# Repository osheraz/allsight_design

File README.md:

# allsight_design

Manufacturing design files for the [AllSight tactile sensor](https://github.com/osheraz/allsight).

## Content

This repository aims to provide manufacturing, assembly, and quick-start instruction for the AllSight tactile sensor.

## Quick Start

Manufacturing and assembly documentation is found in the [Quick Start Guide](https://docs.google.com/document/d/1w17rNp5aecgzT3BPEN_t8wV7Ci-CQgCzxq583NlFb_A/edit?usp=sharing)

## Questions and Contributing

If you have questions or need help with the content of this repo please open a ticket.

## License
These design files are licensed under CC-by-NC, as found in the [LICENSE](LICENSE) file.

## Citing
If you use this project in your research, please cite this [paper](https://arxiv.org/abs/2307.02928):

```BibTeX
@misc{azulay2023allsight,
      title={AllSight: A Low-Cost and High-Resolution Round Tactile Sensor with Zero-Shot Learning Capability}, 
      author={Osher Azulay and Nimrod Curtis and Rotem Sokolovsky and Guy Levitski and Daniel Slomovik and Guy Lilling and Avishai Sintov},
      year={2023},
      eprint={2307.02928},
      archivePrefix={arXiv},
      primaryClass={cs.RO}
}

```

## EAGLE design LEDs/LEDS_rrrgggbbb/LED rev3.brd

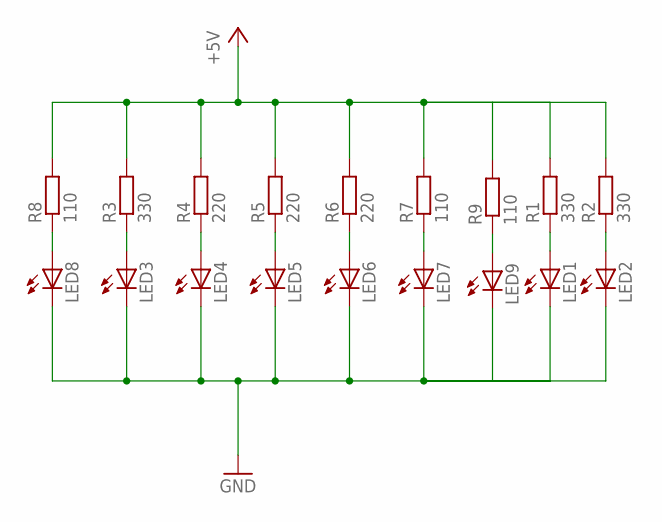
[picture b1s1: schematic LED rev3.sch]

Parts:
LED1, LED2, LED3, LED4, LED5, LED6, LED7, LED8, LED9: LEDCHIPLED_0603; CHIPLED_0603
R1, R2, R3: 330; R0603
R4, R5, R6: 220; R0603
R7, R8, R9: 110; R0603

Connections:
+5V: R1.2, R2.2, R3.2, R4.2, R5.2, R6.2, R7.2, R8.2, R9.2
GND: LED1.C, LED2.C, LED3.C, LED4.C, LED5.C, LED6.C, LED7.C, LED8.C, LED9.C
unnamed: LED8.A, R8.1
unnamed: LED7.A, R7.1
unnamed: LED3.A, R3.1
unnamed: LED4.A, R4.1
unnamed: LED5.A, R5.1
unnamed: LED6.A, R6.1
unnamed: LED9.A, R9.1
unnamed: LED1.A, R1.1
unnamed: LED2.A, R2.1

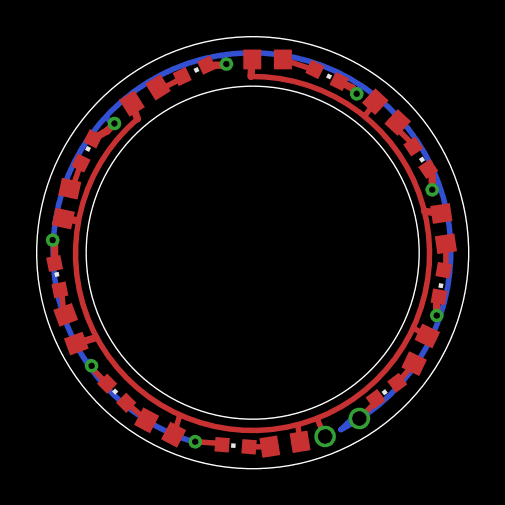
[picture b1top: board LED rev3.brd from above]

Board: 2 copper layers, 24.0 x 24.0 mm, 18 parts (0 on the bottom side), 11 nets.

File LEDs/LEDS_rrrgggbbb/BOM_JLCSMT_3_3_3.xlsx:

Comment | Designator | Footprint | JLCPCB Part #（optional）
220ohms | R4, R5, R6 | R0603
330ohms | R1, R2, R3 | R0603
110ohms | R7, R8, R9 | R0603
Green LED | LED1, LED2, LED3 | CHIPLED-0603 | C118334
Blue LED | LED4, LED5, LED6 | CHIPLED-0603 | C118339
Red LED | LED7, LED8, LED9 | CHIPLED-0603 | C118330

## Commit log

2023-05-21 first push
2023-05-21 added readme
2023-07-10 Create LICENSE

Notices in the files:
README.md:
License: CC BY-NC 4.0
